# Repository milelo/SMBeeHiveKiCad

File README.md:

# SMBeeHiveKiCad

Anybody making an [SMBee] needs access to a programmer.

This is a low cost custom programmer you can use to give an SMBee a one-time programme or develope custom LED sequences for it. It uses the cheap widely available USBASP ISP programming module that you can purchase and re-flash with the required [custom firmware][SMBeeHive USBASP firmware].

There are two associated GitHub repositories:
* The case / jig design and laser cutter PDF: [SMBeeHive case]
* The custom USBASP firmware and reprogramming instructions: [SMBeeHive USBASP firmware].

---

**A fully assembled unit.** The USB programmer on the right is inexpensive, easily sourced and can be easily reprogrammed to support the project.

---

Top | Bottom
:-:|:-:
 | 
 | 

**The programmer PCB design images and a completed PCA.**

<!-- {:width="10px"} {:width="10px"}> -->

# Manufacturing Data

This is the information you need to have SMBeeHive PCBs manufactured.

## Gerber files

Generated gerber files for SMBeeHive version:

SMBeeHive | Generated with KiCad | Download 
-|-|-
1.2 (latest)| 5.0.2-5-10.14 | [SMBeeHive1.2.zip]

Typically just send the zip. The file formats and identifying file extensions will be accepted by most manufacturers including:

* [ELECROW]
* [PCBs.io]
* [AISLER]

See the [SMBeeHive PCB costs] spreadsheet for more information on manufacturers.

## Manufacturing options

Some manufacturers have additional options that need to be specified:

Parameter | Value |
-|-
Layers | 2 |
Thickness | 1.6mm |
Finish | HASL lead-free |
Copper weight | 1oz |
PCB colour | *your choice* |
Dimensions | 88 x 76mm |
Castellated holes | no |

# BOM (Build Of Materials)

This is the [SMBeeHive BOM] Spreadsheet. It lists all the required components and suggested and alternate supplies and prices dependant on order quantity.

# Assembly instructions

See the [Project documentation][SMBee].

# Schematic

Key features & operation:
1. The device functions as both a simple power-supply for the docked SMBee and flash memory programmer. For SMBee power-only operation, the USBASP module on J2 can be connected to a USB power supply or power bank.
1. SW1 mirrors the functionality of the SMBee toggle-sleep switch which isn't accessible when docked.
1. The docked SMBee connects to J1.
1. R1 limits the SMBee LED current for operation from a 3V or 5V supply voltage. The voltage is selectable with the USBASP J1 link and only affects LED brightness while docked.
1. The S10V2F12 DC-DC convertor on J3 generates the 12V Vpp programming voltage during SMBee programming. It is controlled by the USBASP custom firmware.
1. PRG is active at 12V only during programming, then removed, SMbee execute its new firmware when PRG is removed.
1. D1 is a Schottkey diode for low forward volt-drop. The diode prevents the DC-DC converter output from sinking current when it is disabled.
1. R2 limits the DC-DC current for protection if SW1 is pressed during programming.
1. JP1 is for manual programming voltage control. It is isn't used with the custom USBASP firmware and relies on the default link track; the USBASP reset signal has been repurposed to supply the DC-DC converter providing the 12V programming voltage to PRG.
1. The SMBee battery should be removed when connected to prevent charging of its primary cell. The case provides a mechanical lockout to prevent docking with the battery inserted.

# View or edit the PCB design

The PCB was designed using KiCad EDA software. If you would like to view or edit the design files, download it from [KiCad download] and install the software. 

Clone this repository into your local file space and open SMBeeHive.pro.

# SMBeeHive case

The case also performs as a jig to position the SMBee against the contact pins. It can be laser cut from 3mm acrylic sheet. You can find the details here:  [SMBeeHive case].

[SMBee]: https://github.com/milelo/SMBee
[SMBeeHive USBASP firmware]: https://github.com/milelo/SMBeeHiveFirmware
[HIVE-BOM]: https://docs.google.com/spreadsheets/d/1pC-4M-7qa12mT0QL2S9FdDb4QyRmq4kYofQHElQal1s/edit#gid=64958878
[SMBeeHive PCB costs]: https://docs.google.com/spreadsheets/d/1pC-4M-7qa12mT0QL2S9FdDb4QyRmq4kYofQHElQal1s/edit#gid=258570514
[ELECROW]: https://www.elecrow.com/pcb-manufacturing.html
[PCBs.io]: https://www.pcbs.io/
[AISLER]: https://aisler.net/
[SMBeeHive BOM]: https://docs.google.com/spreadsheets/d/1pC-4M-7qa12mT0QL2S9FdDb4QyRmq4kYofQHElQal1s/edit#gid=64958878
[KiCad download]: http://kicad-pcb.org/download/.
[SMBeeHive case]: https://github.com/milelo/SMBeeHiveF360
[SMBeeHive1.2.zip]: https://github.com/milelo/SMBeeHiveKiCad/blob/master/gerber/SMBeeHive1.2.zip?raw=true

---

This work is Copyright © 2019 Mike Longworth

<br />This work is licensed under a <a rel="license" href="http://creativecommons.org/licenses/by/4.0/">Creative Commons Attribution 4.0 International License</a>.

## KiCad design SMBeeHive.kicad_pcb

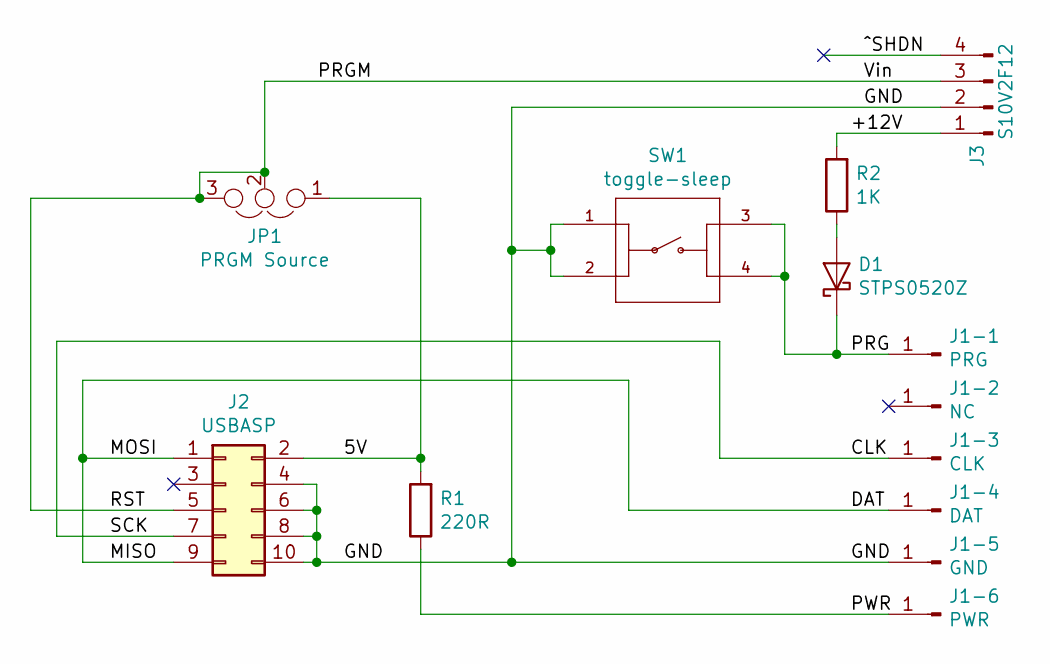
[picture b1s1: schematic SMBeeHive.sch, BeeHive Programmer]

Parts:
D1: STPS0520Z; D_SOD-123
J1-1: PRG; Pin-0906-1-15-20-7X-14-11-0
J1-2: NC; Pin-0906-1-15-20-7X-14-11-0
J1-3: CLK; Pin-0906-1-15-20-7X-14-11-0
J1-4: DAT; Pin-0906-1-15-20-7X-14-11-0
J1-5: GND; Pin-0906-1-15-20-7X-14-11-0
J1-6: PWR; Pin-0906-1-15-20-7X-14-11-0
J2: USBASP; Pin_Header_Straight_2x05_Pitch2.54mm
J3: S10V2F12; Pin_Header_Straight_1x04_Pitch2.54mm
JP1: PRGM Source; Pin_Header_Straight_1x03_Pitch2.54mm
R1: 220R; R_0805_HandSoldering
R2: 1K; R_0805_HandSoldering
SW1: toggle-sleep; SW_1825910-6

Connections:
/5V: J2.2, JP1.1, R1.2
/+12V: J3.1, R2.2
/CLK: J1-3.1, J2.7
/DAT: J1-4.1, J2.1, J2.9
/GND: J1-5.1, J2.4, J2.6, J2.8, J2.10, J3.2, SW1.1, SW1.2; also elsewhere on the board
/PRGM: J2.5, J3.3, JP1.2, JP1.3
/PWR: J1-6.1, R1.1
/RST: D1.1 (K), J1-1.1, SW1.3, SW1.4; also elsewhere on the board
/^SHDN: J3.4
unnamed: D1.2 (A), R2.1

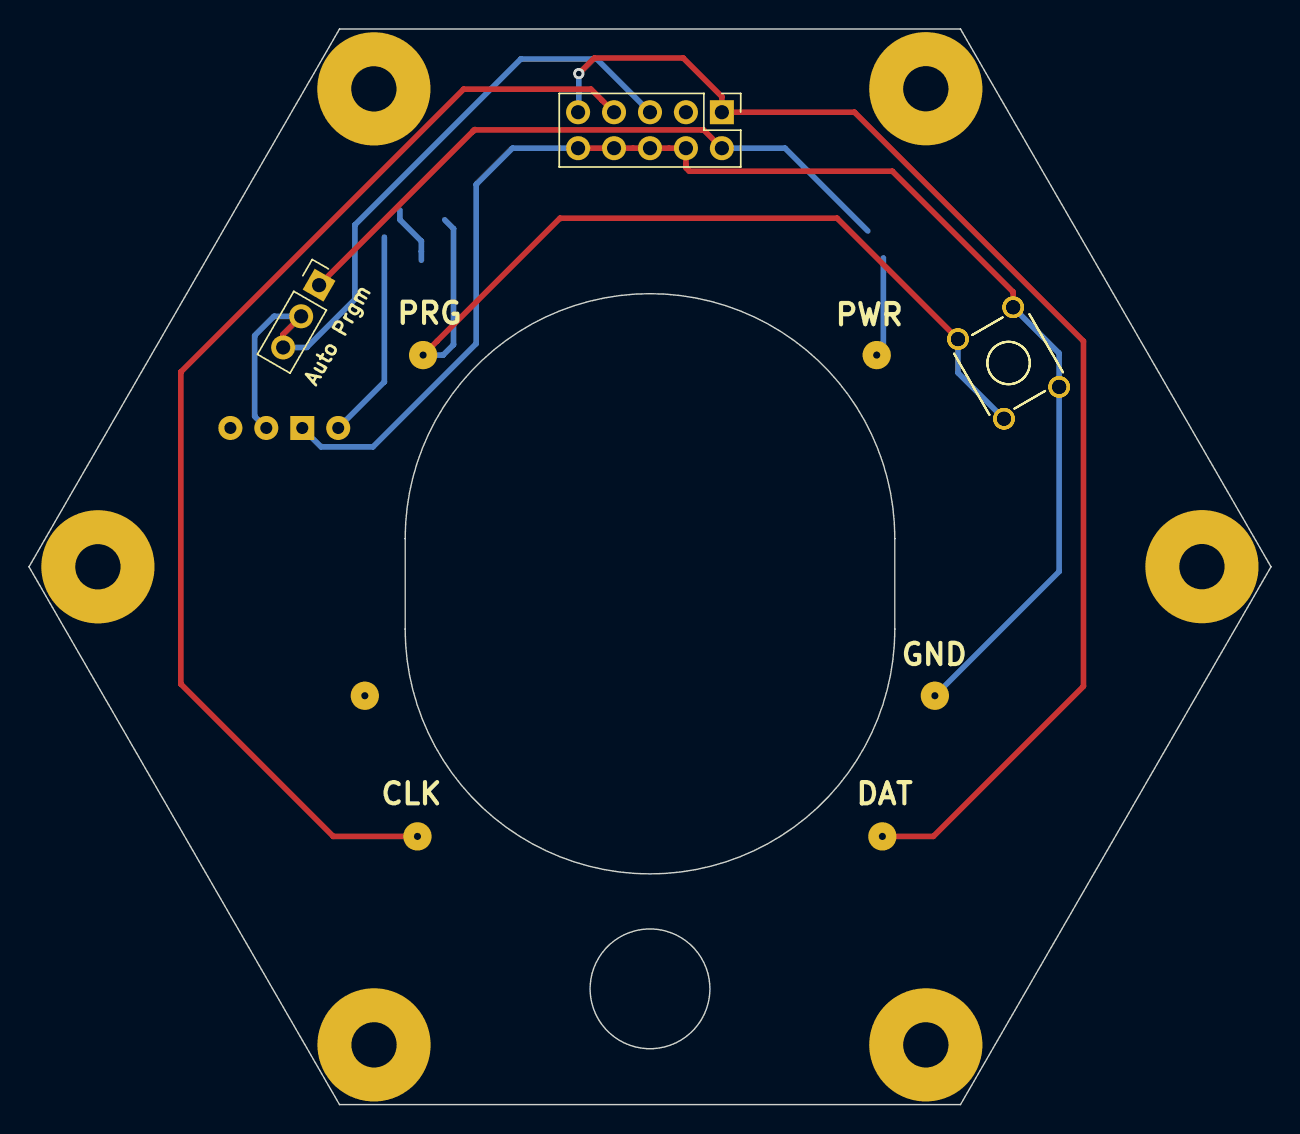
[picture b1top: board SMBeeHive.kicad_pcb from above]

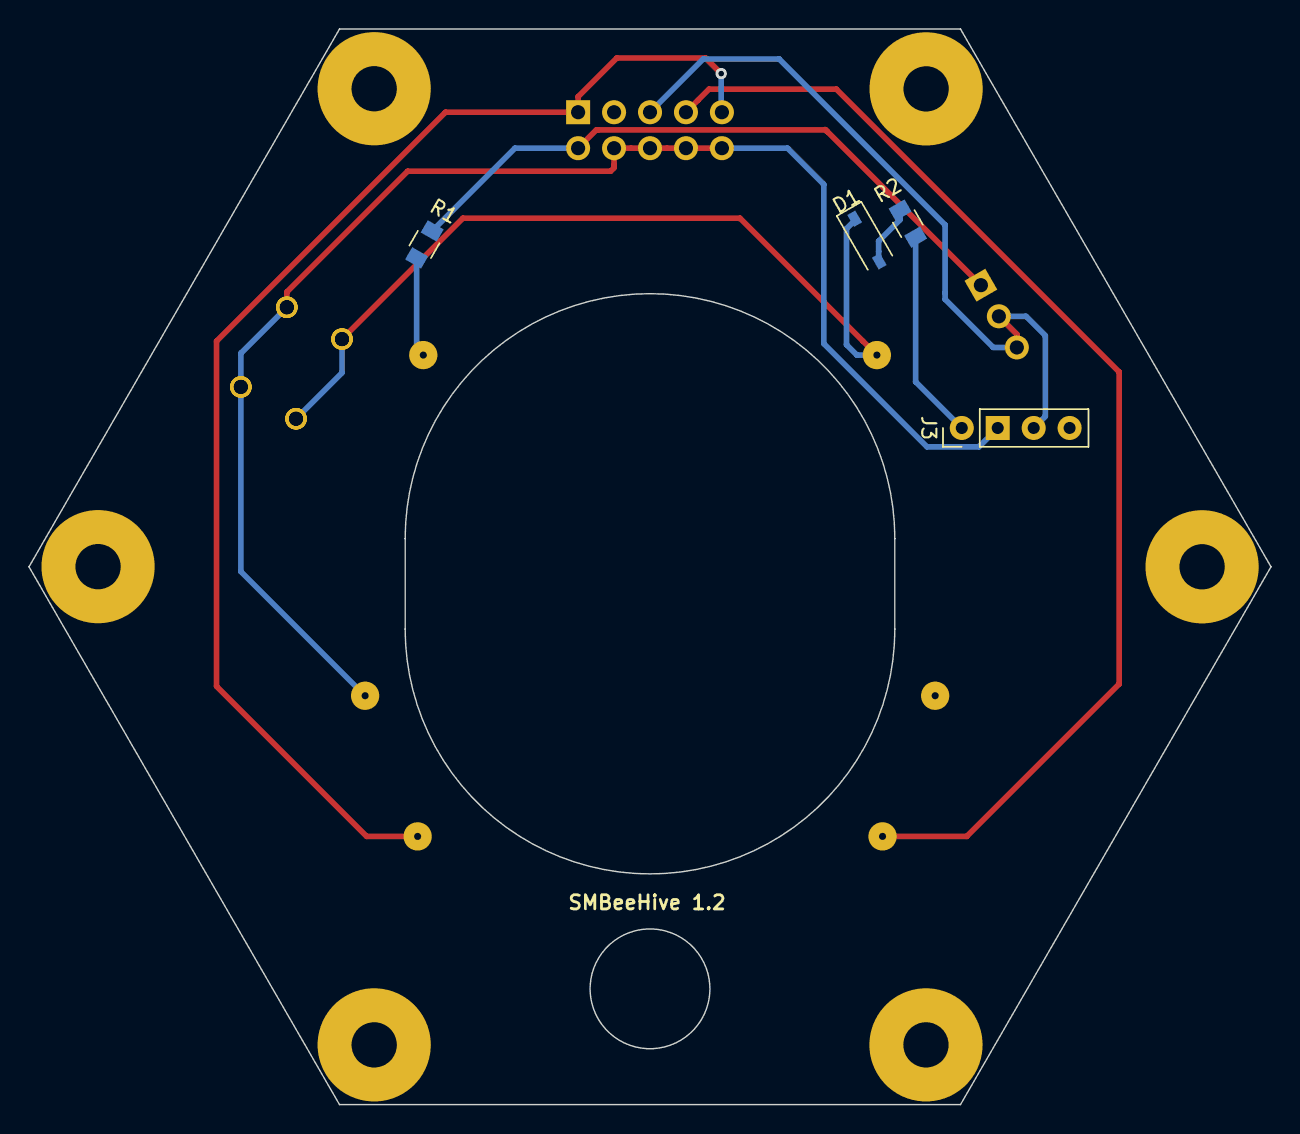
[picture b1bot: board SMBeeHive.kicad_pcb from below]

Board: 2 copper layers, 87.8 x 76.0 mm, 14 parts (4 on the bottom side), 9 nets.

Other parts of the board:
SW1#2: toggle-sleep; SW_1825910-6

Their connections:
/GND: SW1#2.1, SW1#2.2; also elsewhere on the board
/RST: SW1#2.3, SW1#2.4; also elsewhere on the board

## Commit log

2019-02-27 V1.1
2019-02-27 1.1.1
    Add solder mask to mount holes
2019-02-27 Revert "1.1.1"
    This reverts commit cb8728db90ee2a157644e88719e92d7537fd437a.
2019-02-27 Revert "Revert "1.1.1""
    This reverts commit 3620604aef5e1d868b8234b776ffff62c005b7fe.
2019-03-12 Move converter for cut-out 1.1->1.2
2019-05-30 Add doc files
2019-08-05 KiCad 5.0.2-5-10.14
2019-08-27 Development updates
2019-08-29 interim updates
2019-09-30 License
2019-10-01 Dev updates
